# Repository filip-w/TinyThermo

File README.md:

# TinyThermo
Low-cost and accurate open source thermocouple to CAN module for the DIY enthusiast.

Modular design, with readily available modules.
Based on Arduino Nano, MAX31855 and MCP2515 CAN-module.

Librarys used
- FIR filter by Leeman Geophysical LLC
- autowp-mcp2515 by autowp
- Adafruit MAX31855 library by Adafruit

## Hardware

### Connectors
Use only **Type K Miniature Mini plug**
- Keep in mind that it is polarity sensitive and only fits in one direction.
- Keep in mind that the Thermocouple contact is sensitive to torsion and tensile loads.

**M12 5 Pin A coded Female**

### Tindie Store
I sell both complete kits and bare PCBs on my Tindie store.

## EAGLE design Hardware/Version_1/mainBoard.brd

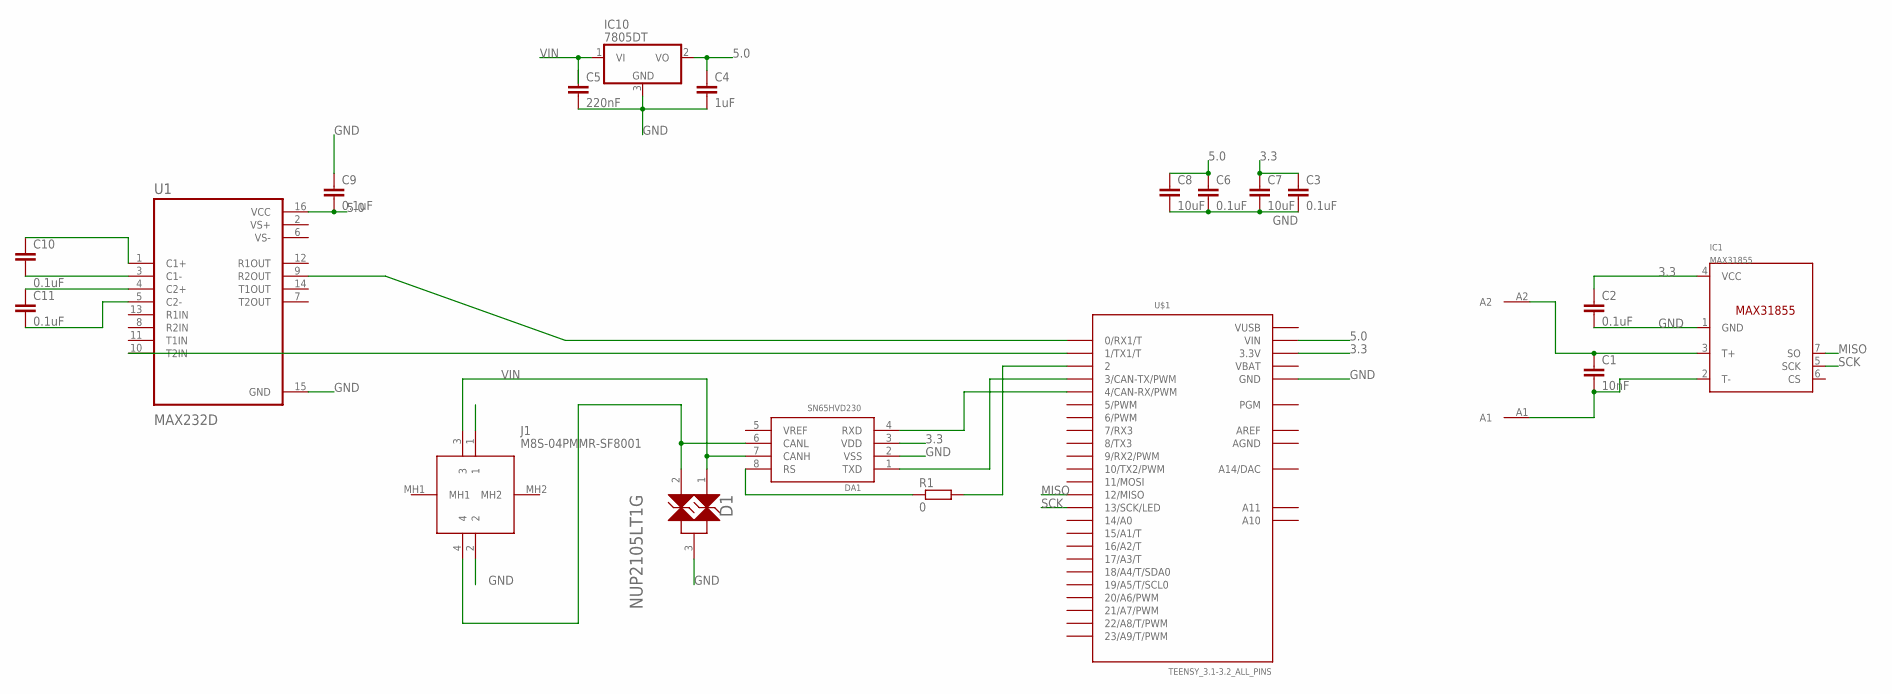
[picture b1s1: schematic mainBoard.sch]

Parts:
C1: 10nF; C0805
C2, C3, C6, C9, C10, C11: 0.1uF; C0805
C4: 1uF; C0805
C5: 220nF; C0805
C7, C8: 10uF; C0805
D1: ON_SEMICONDUCTOR_NUP2105LT1GON_SEMICONDUCTOR_NUP2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; ON_SEMICONDUCTOR_NUP2105LT1G_0
DA1: SN65HVD230; SO08
IC1: MAX31855; SOIC8
IC10: 7805DT; TO252
J1: M8S-04PMMR-SF8001; M8S04PMMRSF8001
R1: 0; R0805
U1: MAX232D; SOIC127P600X175-16N
U$1: TEENSY_3.1-3.2_ALL_PINS; TEENSY_3.0-3.2&LC_ALL_PINS
U$2: PCC-SMD

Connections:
3.3: C2.1, C3.1, C7.1, DA1.3 (VDD), IC1.4 (VCC), U$1.3.3V, U$1.3.3V1 (3.3V)
5.0: C4.1, C6.1, C8.1, C9.2, IC10.2 (VO), U1.16 (VCC), U$1.VIN
AGND: U$1.AGND
AREF: U$1.AREF
GND: C2.2, C3.2, C4.2, C5.2, C6.2, C7.2, C8.2, C9.1, D1.3 (3_K), DA1.2 (VSS), IC1.1 (GND), IC10.3 (GND), J1.2, U1.15 (GND), U$1.GND, U$1.GND1 (GND)
MISO: IC1.7 (SO), U$1.12 (12/MISO)
unnamed: C1.1, IC1.3 (T+), U$2.A2
unnamed: C1.2, IC1.2 (T-), U$2.A1
unnamed: DA1.1 (TXD), U$1.3 (3/CAN-TX/PWM)
unnamed: DA1.4 (RXD), U$1.4 (4/CAN-RX/PWM)
unnamed: R1.2, U$1.2
unnamed: DA1.8 (RS), R1.1
unnamed: C10.1, U1.1 (C1+)
unnamed: C10.2, U1.3 (C1-)
unnamed: C11.2, U1.5 (C2-)
unnamed: C11.1, U1.4 (C2+)
unnamed: U1.10 (T2IN), U$1.1 (1/TX1/T)
unnamed: U1.9 (R2OUT), U$1.0 (0/RX1/T)
unnamed: D1.1 (1_K), DA1.7 (CANH), J1.3
unnamed: D1.2 (2_K), DA1.6 (CANL), J1.4
SCK: IC1.5 (SCK), U$1.13 (13/SCK/LED)
VBAT: U$1.VBAT
VIN: C5.1, IC10.1 (VI), J1.1
VS+: U1.2 (VS+)
VS-: U1.6 (VS-)
VUSB: U$1.VUSB

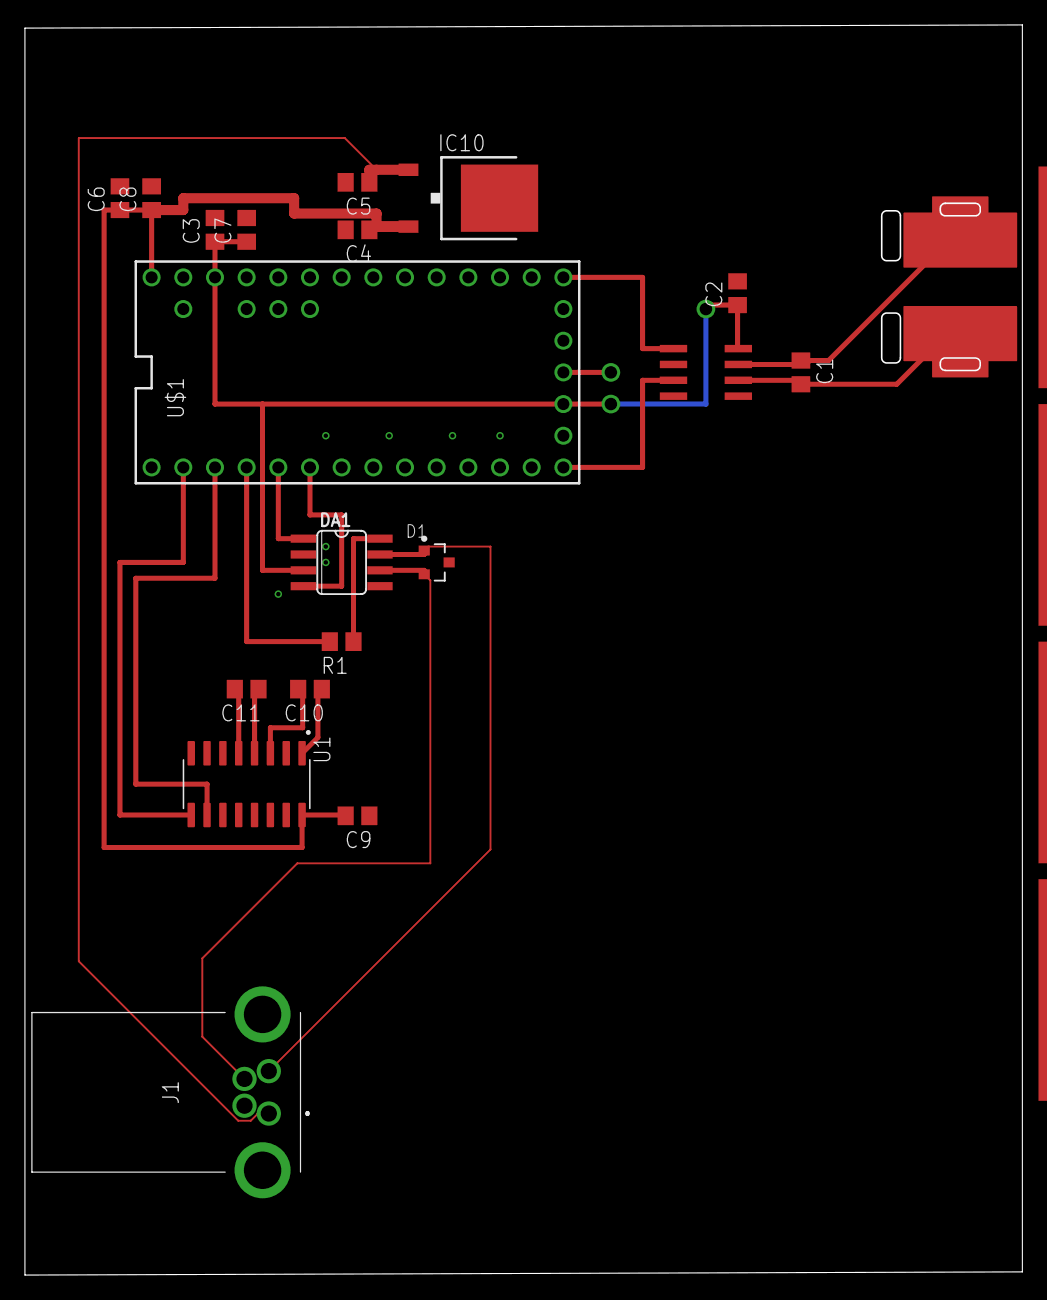
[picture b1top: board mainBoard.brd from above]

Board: 2 copper layers, 79.9 x 100.1 mm, 20 parts (0 on the bottom side), 20 nets.

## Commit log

2022-02-01 Added Hardware folder and Eagle project files
2022-02-01 adding more eagle project files
2022-09-26 Added main program
    Support for 4 channel temperature reading
2022-09-27 Adding support reading settings switches.
2022-09-28 File rename.
2022-09-28 can base id added to can id. crude wait based on updaterate var.
2022-10-05 Added support for CAN module. Send 2 fixed CAN-frames.
2022-10-06 Send temperature over CAN in one message
2022-10-09 Added serialDebug. Fixed delay bug.
2022-10-10 Added DBC
2022-10-10 Trying out FIR filter library. Creating struct for thermocouple channels.
2022-10-11 Using struct for thermocouple channels.
2022-10-13 Adding support for CAN baudrate switch setting.
2022-10-14 Adding support for 1 sec avg FIR filter
2022-10-19 Adding schematic
2022-10-19 Clean up
2022-10-28 Adding BOM-list
2022-11-24 Wrong box, changing article number in BOM
2022-12-05 Rename files
2025-02-18 Update README.md
    librarys in list
2025-12-13 Update README with hardware and Tindie store info
    Added hardware connectors section and Tindie store link.
2026-03-10 Enhance README with images and hardware details
    Added images to README and expanded hardware section.
